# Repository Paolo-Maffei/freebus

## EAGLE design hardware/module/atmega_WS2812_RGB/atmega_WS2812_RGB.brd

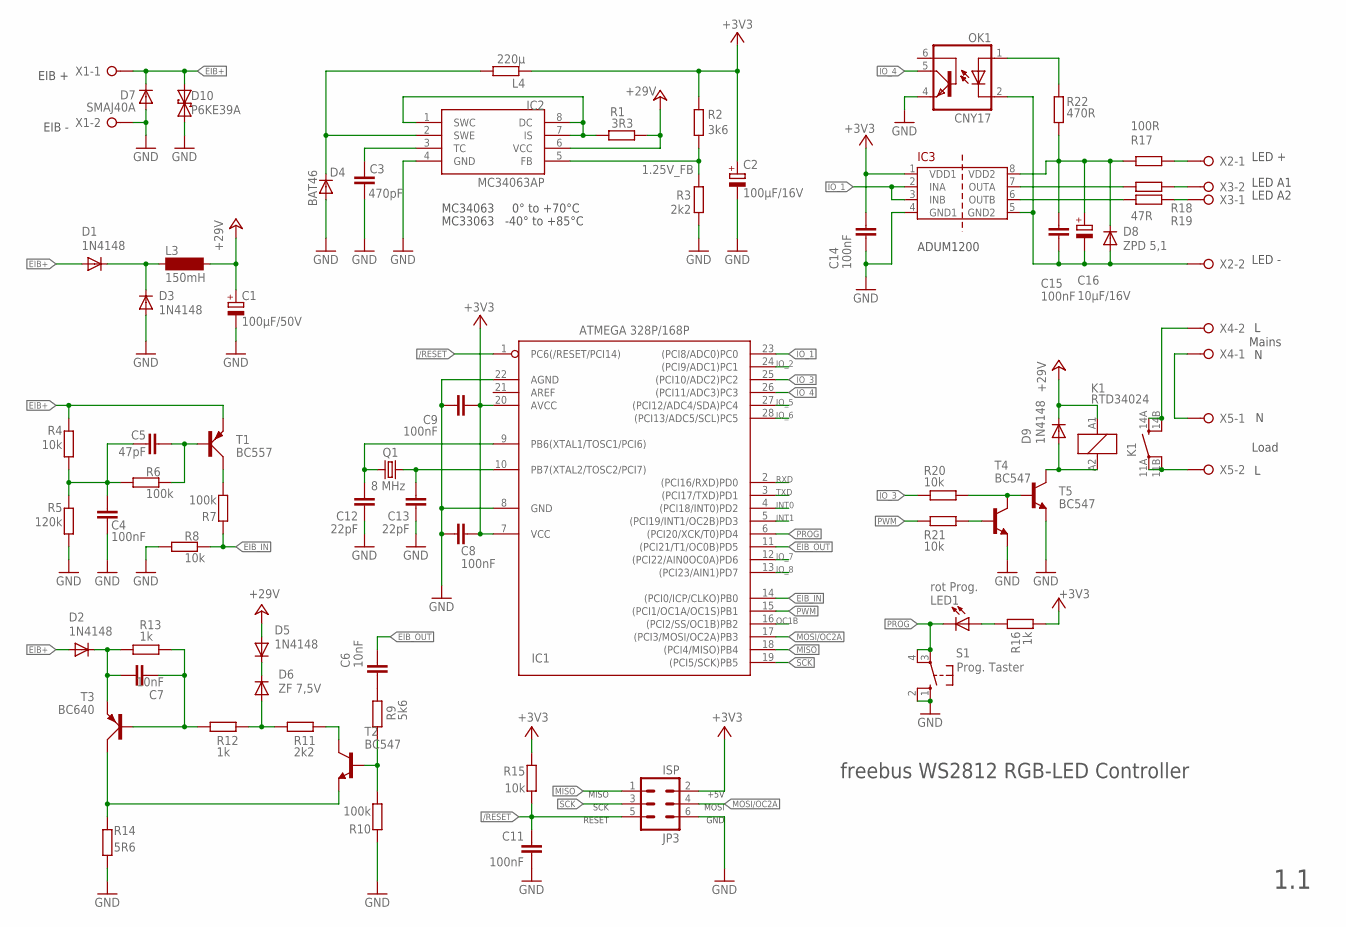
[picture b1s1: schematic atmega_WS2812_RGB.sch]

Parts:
C1: 100µF/50V; E3,5-8
C2: 100µF/16V; E3,5-8
C3: 470pF; C025-024X044
C4, C8, C9, C11, C14, C15: 100nF; C025-024X044
C5: 47pF; C025-024X044
C6, C7: 10nF; C025-024X044
C12, C13: 22pF; C025-024X044
C16: 10µF/16V; E2-5
D1, D2, D3, D5, D9: 1N4148; DO34-7R
D4: BAT46; DO34-7R
D6: ZF 7,5V; DO34-7R
D7: SMAJ40A; SMB
D8: ZPD 5,1; DO34-7R
D10: P6KE39A; DO41-7
IC1: ATMEGA 328P/168P; DIL28-3
IC2: MC34063AP; DIL08
IC3: ADUM1200; SO8
JP3: ISP; ML6
K1: RTD34024; RT-N/O16A5
L3: 150mH; BS11
L4: 220µ; 0309/12
LED1: rot Prog.; LED3MM
OK1: CNY17; DIL06
Q1: 8 MHz; HC49U-V
R1: 3R3; 0207/7
R2: 3k6; 0207/7
R3, R11: 2k2; 0207/7
R4, R8, R15, R20, R21: 10k; 0207/7
R5: 120k; 0207/7
R6, R7, R10: 100k; 0207/7
R9: 5k6; 0207/7
R12, R13, R16: 1k; 0207/7
R14: 5R6; 0207/7
R17: 100R; 0207/7
R18, R19: 47R; 0207/7
R22: 470R; 0207/7
S1: Prog. Taster; B3F-10XX
T1: BC557; SOT54A
T2, T4, T5: BC547; TO92
T3: BC640; SOT54D
X1, X2, X3, X4, X5: W237-02P; W237-132

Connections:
1.25V_FB: IC2.5 (FB), R2.2, R3.2
+3V3: C2.+, C8.1, C9.1, C14.2, IC1.7 (VCC), IC1.20 (AVCC), IC3.1 (VDD1), JP3.2, L4.1, R2.1, R15.2, R16.2
+24V: C1.+, D5.A, D9.C, IC2.6 (VCC), K1.A1 (1), L3.2, R1.1
/RESET: C11.2, IC1.1 (PC6(/RESET/PCI14)), JP3.5, R15.1
EIB+: D1.A, D2.A, D7.1 (C), D10.C (2), R4.2, T1.E, X1.1
EIB_IN: IC1.14 ((PCI0/ICP/CLKO)PB0), R7.2, R8.2
EIB_OUT: C6.2, IC1.11 ((PCI21/T1/OC0B)PD5)
GND: C1.-, C2.-, C3.1, C4.1, C8.2, C9.2, C11.1, C12.2, C13.2, C14.1, D3.A, D4.A, D7.2 (A), D10.A (1), IC1.8 (GND), IC1.22 (AGND), IC2.4 (GND), IC3.4 (GND1), JP3.6, OK1.4 (EMI), R3.1, R5.1, R8.1, R10.2, R14.1, S1.1 (S), S1.2 (S1), T4.1 (E), T5.1 (E), X1.2
INT0: IC1.4 ((PCI18/INT0)PD2)
INT1: IC1.5 ((PCI19/INT1/OC2B)PD3)
IO_1: IC1.23 ((PCI8/ADC0)PC0), IC3.2 (INA), IC3.3 (INB)
IO_2: IC1.24 ((PCI9/ADC1)PC1)
IO_3: IC1.25 ((PCI10/ADC2)PC2), R20.1
IO_4: IC1.26 ((PCI11/ADC3)PC3), OK1.5 (COL)
IO_5: IC1.27 ((PCI12/ADC4/SDA)PC4)
IO_6: IC1.28 ((PCI13/ADC5/SCL)PC5)
IO_7: IC1.12 ((PCI22/AIN0OC0A)PD6)
IO_8: IC1.13 ((PCI23/AIN1)PD7)
MISO: IC1.18 ((PCI4/MISO)PB4), JP3.1
MOSI/OC2A: IC1.17 ((PCI3/MOSI/OC2A)PB3), JP3.4
unnamed: R18.1, X3.2
unnamed: C15.2, C16.+, D8.C, IC3.8 (VDD2), R17.1, R22.1
unnamed: IC3.7 (OUTA), R18.2
unnamed: IC3.6 (OUTB), R19.2
unnamed: X4.1, X5.1
unnamed: R17.2, X2.1
unnamed: R21.2, T4.2 (B)
unnamed: R19.1, X3.1
unnamed: LED1.A, R16.1
unnamed: R20.2, T4.3 (C), T5.2 (B)
unnamed: K1.11A (PA), K1.11B (PB), X5.2
unnamed: C4.2, C5.1, R4.1, R5.2, R6.2
unnamed: R7.1, T1.C
unnamed: K1.14A (SA), K1.14B (SB), X4.2
unnamed: IC2.1 (SWC), IC2.7 (IS), IC2.8 (DC), R1.2
unnamed: D1.C, D3.C, L3.1
unnamed: C6.1, R9.1
unnamed: R9.2, R10.1, T2.2 (B)
unnamed: C7.2, R12.1, R13.1, T3.B
unnamed: OK1.1 (A), R22.2
unnamed: D5.C, D6.C
unnamed: D4.C, IC2.2 (SWE), L4.2
unnamed: C3.2, IC2.3 (TC)
unnamed: D6.A, R11.2, R12.2
unnamed: C5.2, R6.1, T1.B
unnamed: R11.1, T2.3 (C)
unnamed: R14.2, T2.1 (E), T3.C
unnamed: C7.1, D2.C, R13.2, T3.E
unnamed: C13.1, IC1.10 (PB7(XTAL2/TOSC2/PCI7)), Q1.2
unnamed: C12.1, IC1.9 (PB6(XTAL1/TOSC1/PCI6)), Q1.1
OC1B: IC1.16 ((PCI2/SS/OC1B)PB2)
PROG: IC1.6 ((PCI20/XCK/T0)PD4), LED1.K (C), S1.3, S1.4 (P1)
PWM: IC1.15 ((PCI1/OC1A/OC1S)PB1), R21.1
R4: D9.A, K1.A2 (2), T5.3 (C)
RXD: IC1.2 ((PCI16/RXD)PD0)
SCK: IC1.19 ((PCI5/SCK)PB5), JP3.3
TXD: IC1.3 ((PCI17/TXD)PD1)
WS2812_GND: C15.1, C16.-, D8.A, IC3.5 (GND2), OK1.2 (C), X2.2

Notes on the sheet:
MC34063 0° to +70°C
MC33063 -40° to +85°C
freebus WS2812 RGB-LED Controller
1.1
LED -
LED +
LED A1
LED A2
Mains
Load
ADUM1200
EIB +
EIB -

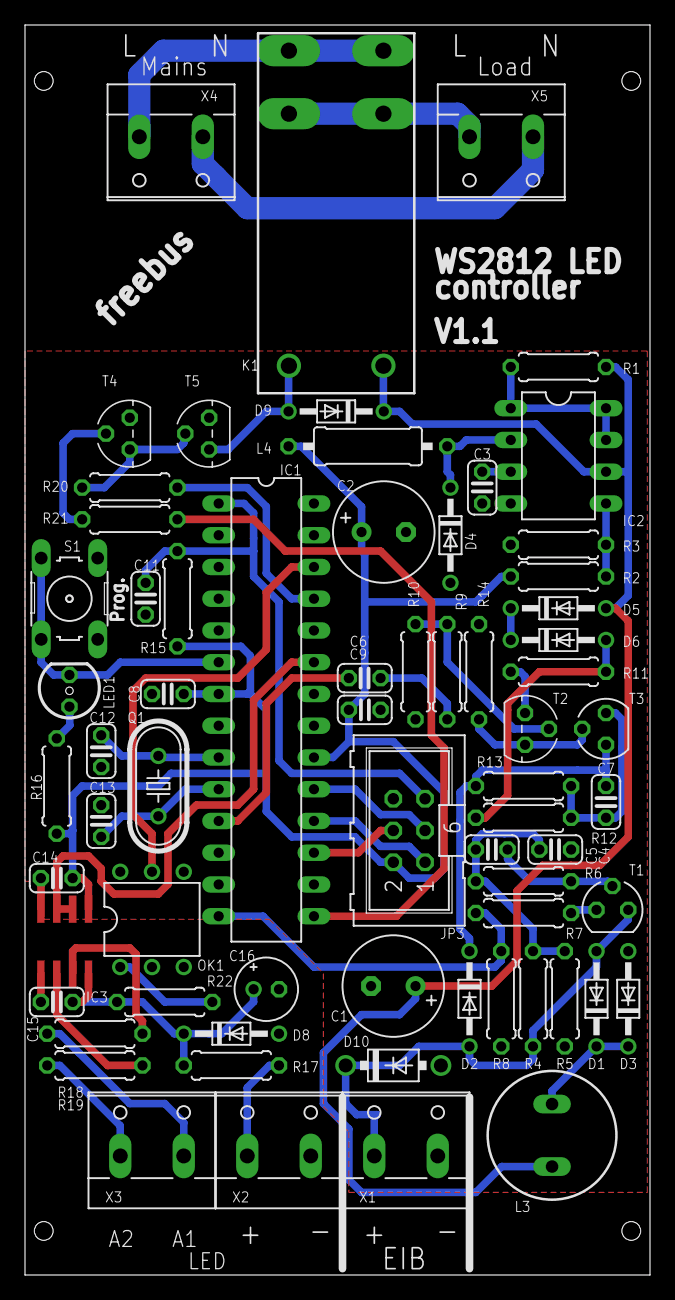
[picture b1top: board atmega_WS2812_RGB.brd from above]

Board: 2 copper layers, 50.0 x 100.0 mm, 68 parts (1 on the bottom side), 48 nets.

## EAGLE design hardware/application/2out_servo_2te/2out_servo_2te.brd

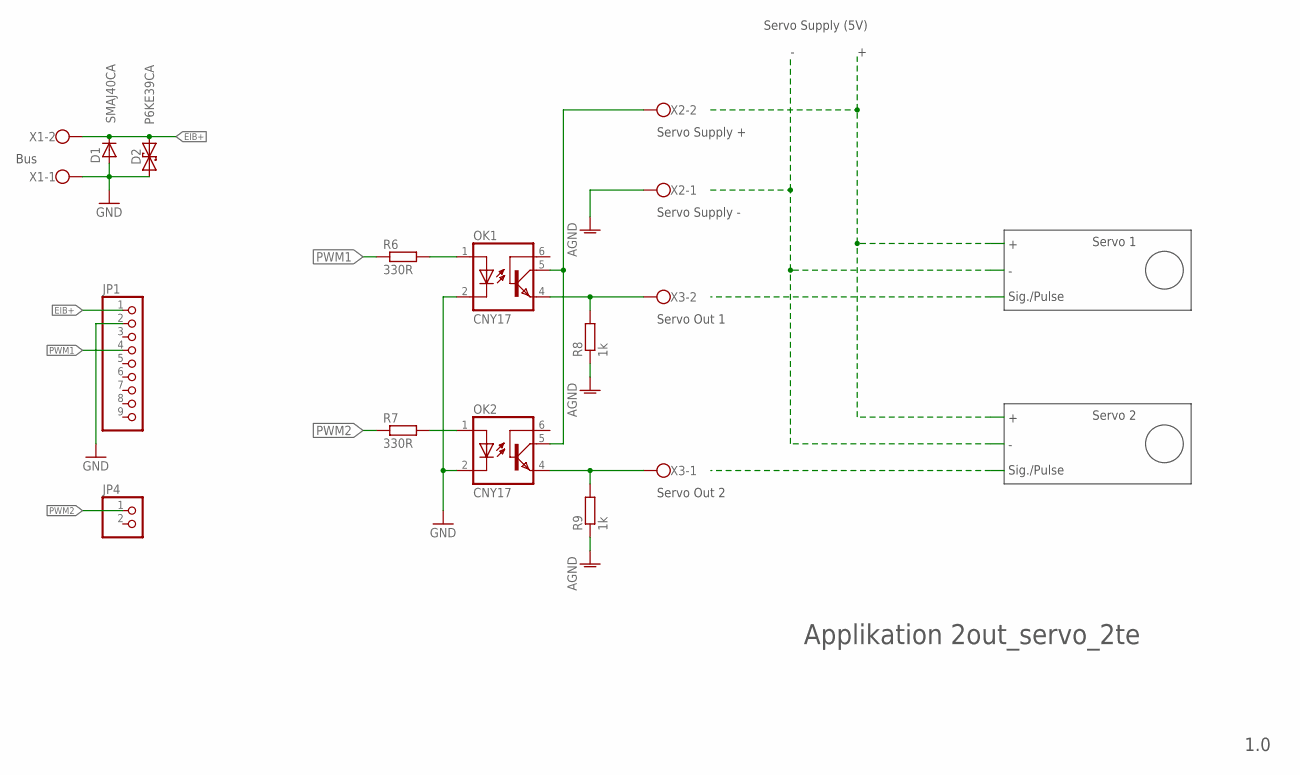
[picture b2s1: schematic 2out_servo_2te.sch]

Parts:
D1: SMAJ40CA; SOD87
D2: P6KE39CA; DO41-7
JP1: PINHD-1X9; 1X09
JP4: PINHD-1X2; 1X02
OK1, OK2: CNY17; DIL06
R6, R7: 330R; 0207/7
R8, R9: 1k; 0207/7
X1, X2, X3: W237-02P; W237-132

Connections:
AGND: R8.1, R9.1, X2.1
EIB+: D1.1 (C), D2.C (2), JP1.1, X1.2
GND: D1.2 (A), D2.A (1), JP1.2, OK1.2 (C), OK2.2 (C), X1.1
unnamed: OK2.1 (A), R7.2
unnamed: OK1.1 (A), R6.2
unnamed: OK1.4 (EMI), R8.2, X3.2
unnamed: OK2.4 (EMI), R9.2, X3.1
unnamed: OK1.5 (COL), OK2.5 (COL), X2.2
PWM1: JP1.4, R6.1
PWM2: JP4.1, R7.1

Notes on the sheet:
Bus
1.0
Applikation 2out_servo_2te
Servo 1
Sig./Pulse
Servo 2
Servo Supply +
Servo Supply -
Servo Out 1
Servo Out 2
Servo Supply (5V)

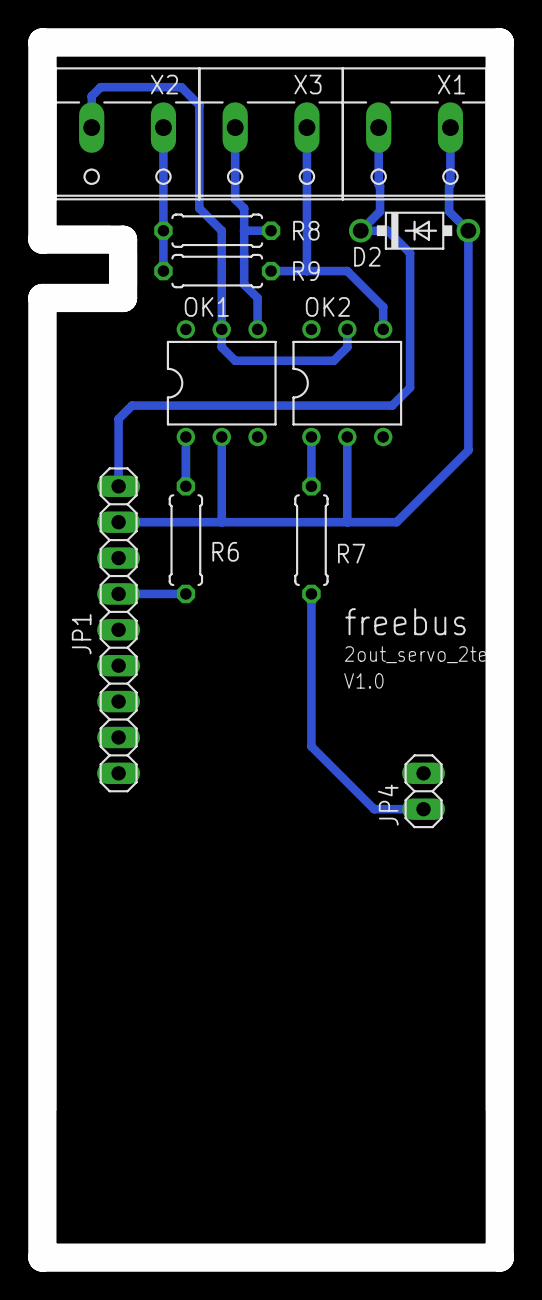
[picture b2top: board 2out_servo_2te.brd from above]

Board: 2 copper layers, 32.4 x 86.0 mm, 13 parts (1 on the bottom side), 10 nets.

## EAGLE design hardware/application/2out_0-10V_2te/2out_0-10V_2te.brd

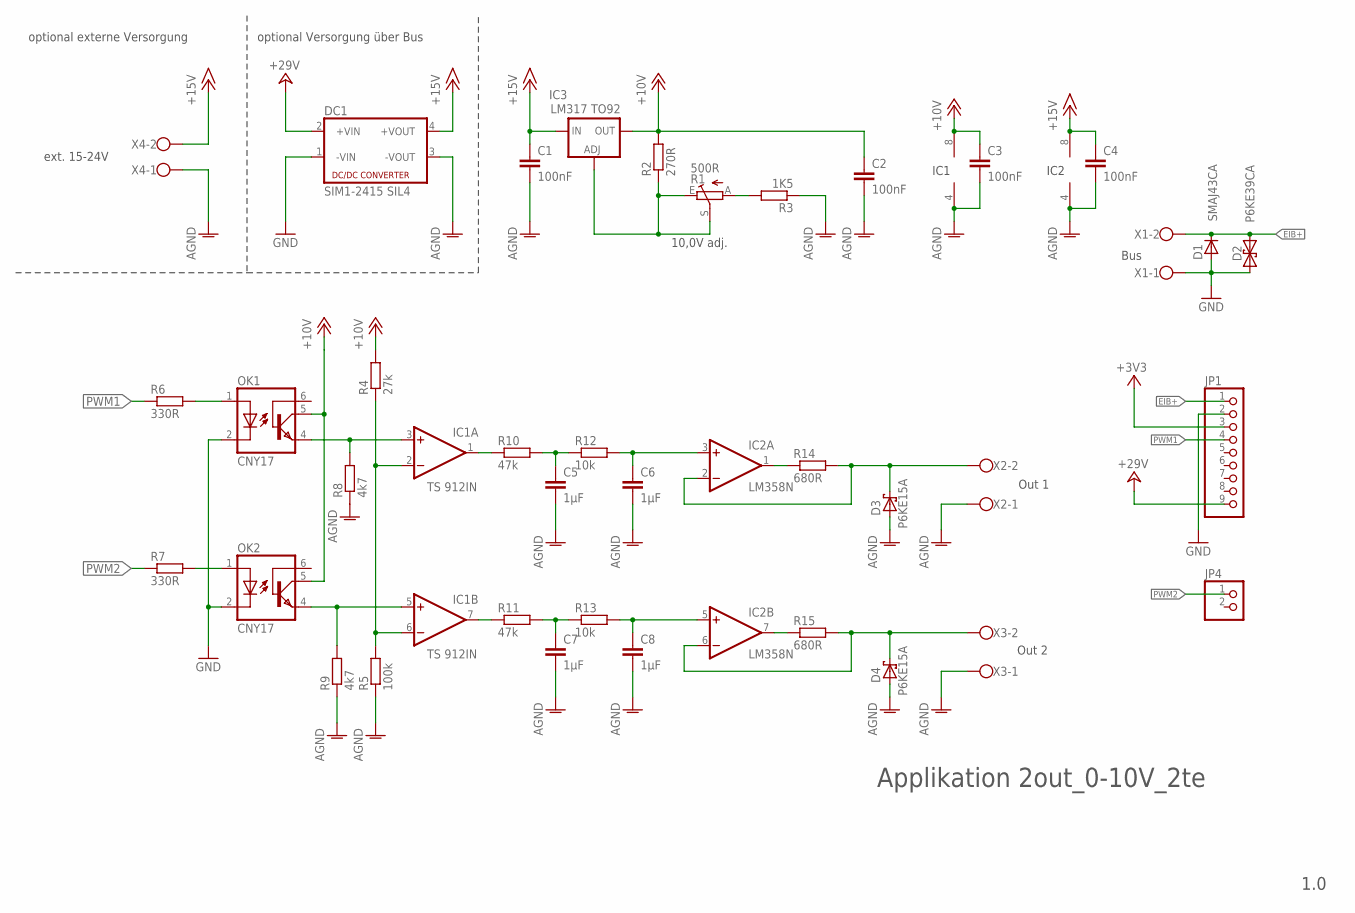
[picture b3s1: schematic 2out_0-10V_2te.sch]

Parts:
C1, C2, C3, C4: 100nF; C025-024X044
C5, C6, C7, C8: 1µF; C050-024X044
D1: SMAJ43CA; SOD87
D2: P6KE39CA; DO41-7
D3, D4: P6KE15A; DO41-7
DC1: SIM1-2415 SIL4; NME
IC1: TS 912IN; DIL08
IC2: LM358N; DIL08
IC3: LM317 TO92; 317L
JP1: PINHD-1X9; 1X09
JP4: PINHD-1X2; 1X02
OK1, OK2: CNY17; DIL06
R1: 500R; B64W
R2: 270R; 0207/7
R3: 1K5; 0207/7
R4: 27k; 0207/7
R5: 100k; 0207/7
R6, R7: 330R; 0207/7
R8, R9: 4k7; 0207/7
R10, R11: 47k; 0207/7
R12, R13: 10k; 0207/7
R14, R15: 680R; 0207/7
X1, X2, X3, X4: W237-02P; W237-132

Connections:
+3V3: JP1.3
+12V: C2.1, C3.1, IC1.8 (V+), IC3.2 (OUT), OK1.5 (COL), OK2.5 (COL), R2.2, R4.2
+15V: C1.1, C4.1, DC1.4 (+VOUT), IC2.8 (V+), IC3.3 (IN), X4.2
+29V: DC1.2 (+VIN), JP1.9
AGND: C1.2, C2.2, C3.2, C4.2, C5.2, C6.2, C7.2, C8.2, D3.A, D4.A, DC1.3 (-VOUT), IC1.4 (V-), IC2.4 (V-), R3.1, R5.1, R8.1, R9.1, X2.1, X3.1, X4.1
EIB+: D1.1 (C), D2.C (2), JP1.1, X1.2
GND: D1.2 (A), D2.A (1), DC1.1 (-VIN), JP1.2, OK1.2 (C), OK2.2 (C), X1.1
unnamed: IC1.7 (OUT), R11.1
unnamed: OK2.1 (A), R7.2
unnamed: OK1.1 (A), R6.2
unnamed: C7.1, R11.2, R13.1
unnamed: IC3.1 (ADJ), R1.E, R1.S, R2.1
unnamed: R1.A, R3.2
unnamed: IC1.3 (+IN), OK1.4 (EMI), R8.2
unnamed: IC1.2 (-IN), IC1.6 (-IN), R4.1, R5.2
unnamed: C8.1, IC2.5 (+IN), R13.2
unnamed: IC2.7 (OUT), R15.1
unnamed: IC1.5 (+IN), OK2.4 (EMI), R9.2
unnamed: IC1.1 (OUT), R10.1
unnamed: C5.1, R10.2, R12.1
unnamed: C6.1, IC2.3 (+IN), R12.2
unnamed: IC2.1 (OUT), R14.1
OUT_1: D3.C, IC2.2 (-IN), R14.2, X2.2
OUT_2: D4.C, IC2.6 (-IN), R15.2, X3.2
PWM1: JP1.4, R6.1
PWM2: JP4.1, R7.1

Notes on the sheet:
Bus
1.0
Applikation 2out_0-10V_2te
ext. 15-24V
Out 1
Out 2
optional externe Versorgung
optional Versorgung über Bus
10,0V adj.
IC1
IC2

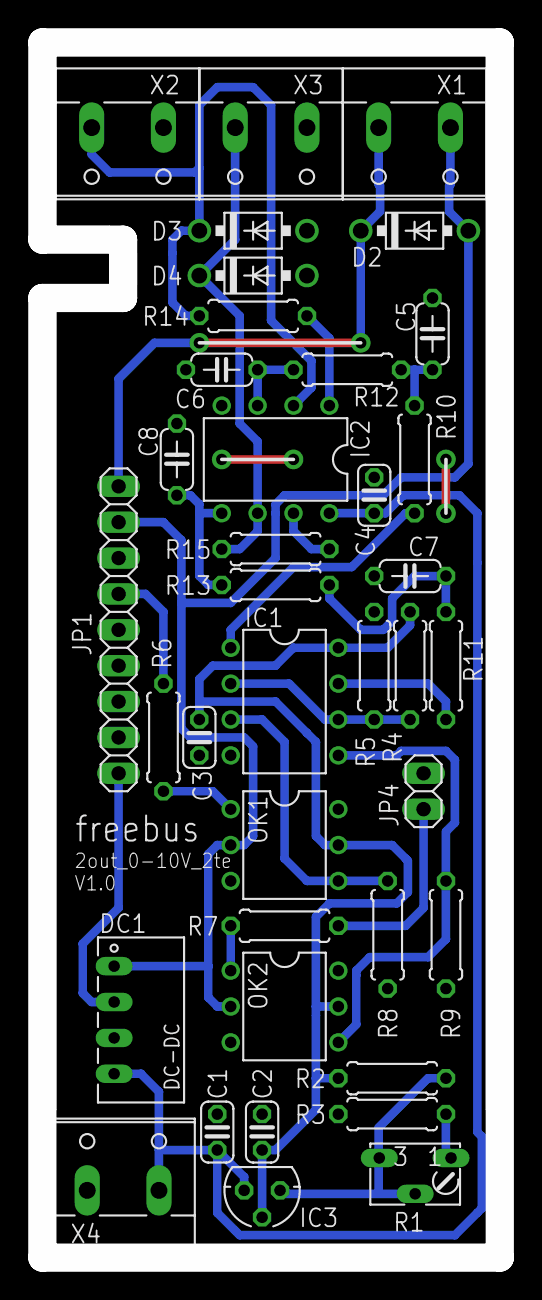
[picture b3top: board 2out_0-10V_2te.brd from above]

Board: 2 copper layers, 32.4 x 86.0 mm, 39 parts (1 on the bottom side), 25 nets.

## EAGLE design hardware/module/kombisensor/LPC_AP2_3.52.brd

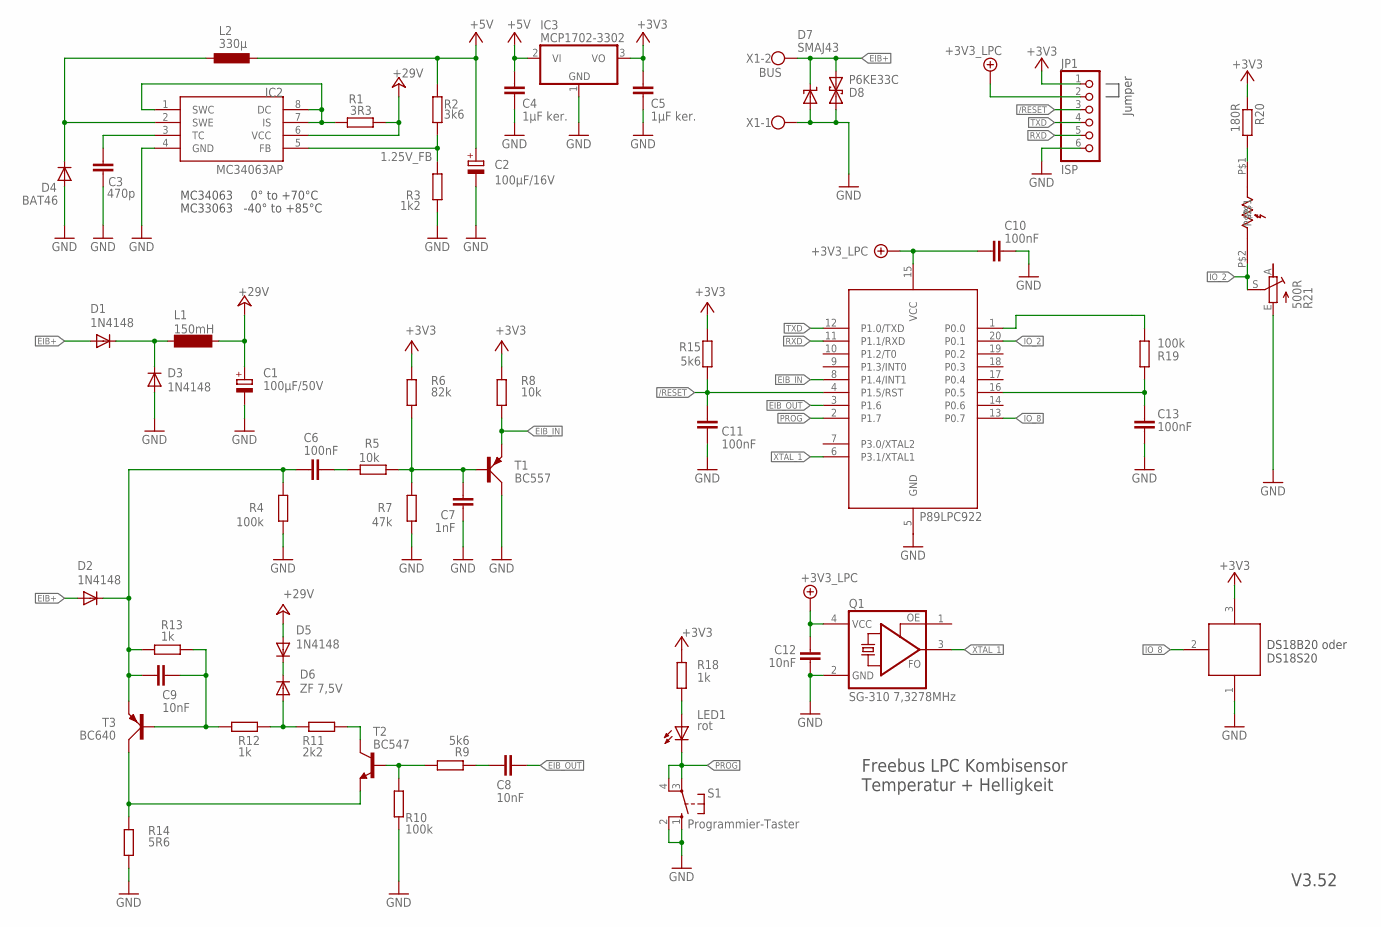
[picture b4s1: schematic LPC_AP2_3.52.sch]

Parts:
C1: 100µF/50V; E3,5-8
C2: 100µF/16V; E2-5
C3: 470p; C025-024X044
C4, C5: 1µF ker.; C050-024X044
C6, C11, C13: 100nF; C050-024X044
C7: 1nF; C050-024X044
C8, C9: 10nF; C050-024X044
C10: 100nF; C0805K
C12: 10nF; C0805K
D1, D3: 1N4148; D-2.5
D2: 1N4148; DO35-7
D4: BAT46; DO34-5R
D5: 1N4148; DO34-5R
D6: ZF 7,5V; DO34-5R
D7: SMAJ43; SMBJ
D8: P6KE33C; DO41-7
IC1: 89LPC922FN; DIL20
IC2: MC34063AP; DIL08
IC3: MCP1702-3302; TO92
IC4: DS18X20; DS18X
JP1: ISP; 1X06
L1: 150mH; SD12K100
L2: 330µ; 0207/7
LDR1: LDR07
LED1: rot; LED3MM
Q1: SG-310 7,3278MHz; ASF
R1: 3R3; 0207/2V
R2: 3k6; 0207/2V
R3: 1k2; 0207/2V
R4, R10: 100k; 0207/2V
R5, R8: 10k; 0207/2V
R6: 82k; 0207/2V
R7: 47k; 0207/2V
R9, R15: 5k6; 0207/2V
R11: 2k2; 0207/2V
R12: 1k; 0207/2V
R13, R18: 1k; 0207/7
R14: 5R6; 0207/2V
R19: 100k; 0207/7
R20: 180R; 0207/2V
R21: 500R; PT6L
S1: Programmier-Taster; B3F-10XX
T1: BC557; SOT54A
T2: BC547; TO92
T3: BC640; SOT54D
X1: BUS; W237-132

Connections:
1.25V_FB: IC2.5 (FB), R2.1, R3.2
+3V3: C5.1, IC3.3 (VO), IC4.3 (VDD), JP1.1, R6.2, R8.2, R15.2, R18.2, R20.1
+4.1V: C10.2, C12.1, IC1.15 (VCC), JP1.2, Q1.4 (VCC)
+5V: C2.+, C4.1, IC3.2 (VI), L2.1, R2.2
+24V: C1.+, D5.A, IC2.6 (VCC), L1.2, R1.1
/RESET: C11.2, IC1.4 (P1.5/RST), JP1.3, R15.1
EIB+: D1.A, D2.A, D7.C, D8.C (2), X1.2
EIB_IN: IC1.8 (P1.4/INT1), R8.1, T1.E
EIB_IN_OUT: C6.1, C9.1, D2.C, R4.2, R13.1, T3.E
EIB_OUT: C8.2, IC1.3 (P1.6)
GND: C1.-, C2.-, C3.1, C4.2, C5.2, C7.1, C10.1, C11.1, C12.2, C13.1, D3.A, D4.A, D7.A, D8.A (1), IC1.5 (GND), IC2.4 (GND), IC3.1 (GND), IC4.1 (GND), JP1.6, Q1.2 (GND), R3.1, R4.1, R7.2, R10.2, R14.1, R21.E, S1.1 (S), S1.2 (S1), T1.C, X1.1
IO_1: IC1.1 (P0.0), R19.1
IO_2: IC1.20 (P0.1), LDR1.P$2, R21.S
IO_6: C13.2, IC1.16 (P0.5), R19.2
IO_8: IC1.13 (P0.7), IC4.2 (IO)
unnamed: C8.1, R9.1
unnamed: C6.2, R5.2
unnamed: D6.A, R11.2, R12.2
unnamed: IC2.1 (SWC), IC2.7 (IS), IC2.8 (DC), R1.2
unnamed: R11.1, T2.3 (C)
unnamed: LDR1.P$1, R20.2
unnamed: R14.2, T2.1 (E), T3.C
unnamed: D1.C, D3.C, L1.1
unnamed: D5.C, D6.C
unnamed: D4.C, IC2.2 (SWE), L2.2
unnamed: R9.2, R10.1, T2.2 (B)
unnamed: C3.2, IC2.3 (TC)
unnamed: C7.2, R5.1, R6.1, R7.1, T1.B
unnamed: C9.2, R12.1, R13.2, T3.B
unnamed: LED1.A, R18.1
PROG: IC1.2 (P1.7), LED1.K (C), S1.3, S1.4 (P1)
RXD: IC1.11 (P1.1/RXD), JP1.5
TXD: IC1.12 (P1.0/TXD), JP1.4
XTAL_1: IC1.6 (P3.1/XTAL1), Q1.3 (FO)

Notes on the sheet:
Freebus LPC Kombisensor Temperatur + Helligkeit
P89LPC922
MC34063 0° to +70°C
MC33063 -40° to +85°C
Jumper
DS18B20 oder DS18S20
V3.52

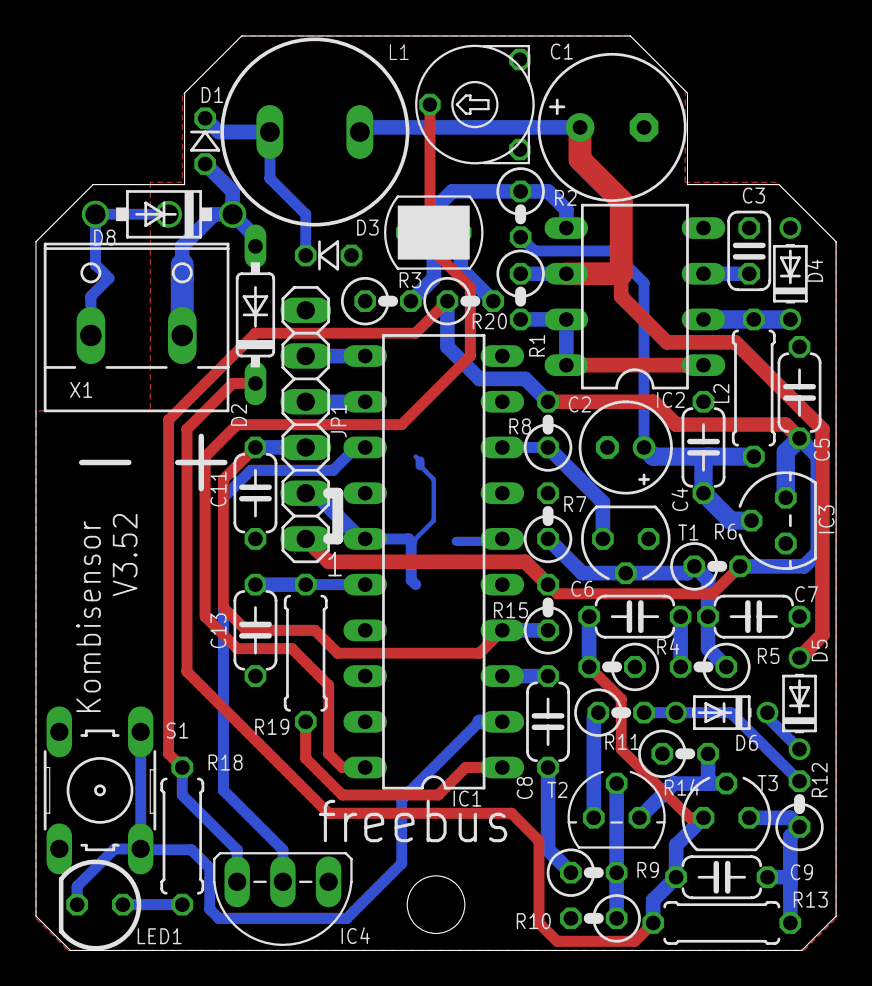
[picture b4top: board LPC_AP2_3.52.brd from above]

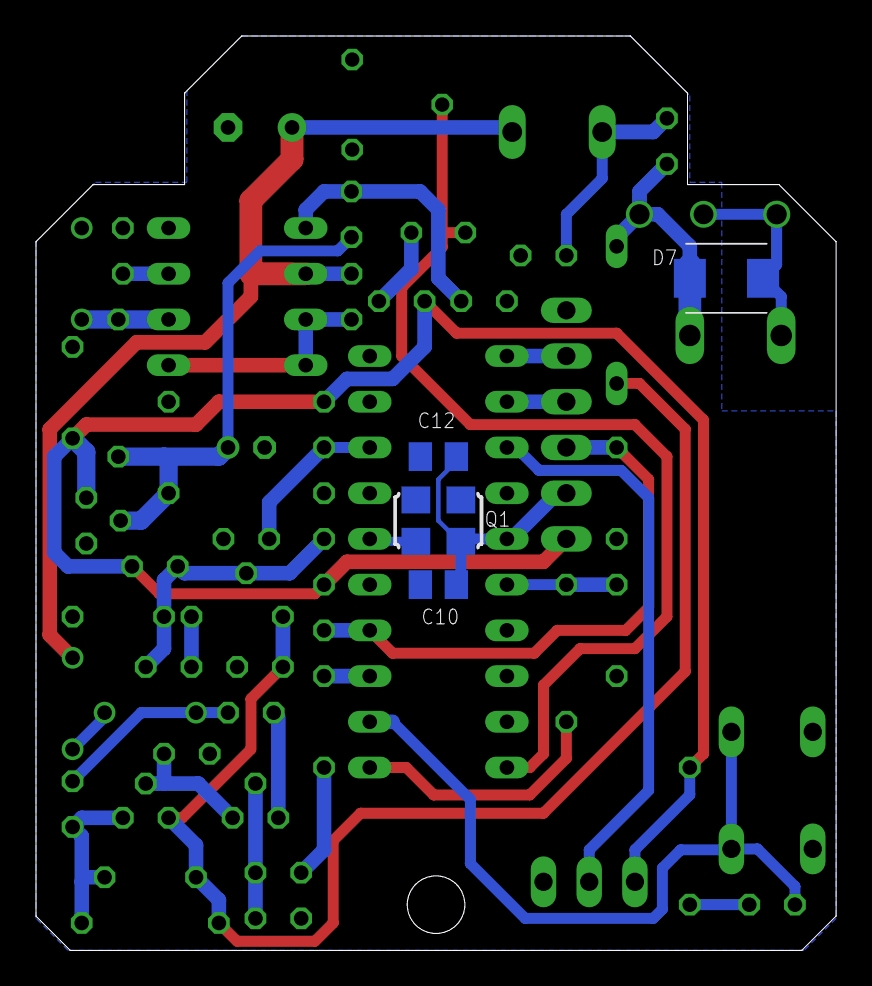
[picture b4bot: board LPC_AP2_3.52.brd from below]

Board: 2 copper layers, 44.5 x 50.8 mm, 55 parts (4 on the bottom side), 34 nets.

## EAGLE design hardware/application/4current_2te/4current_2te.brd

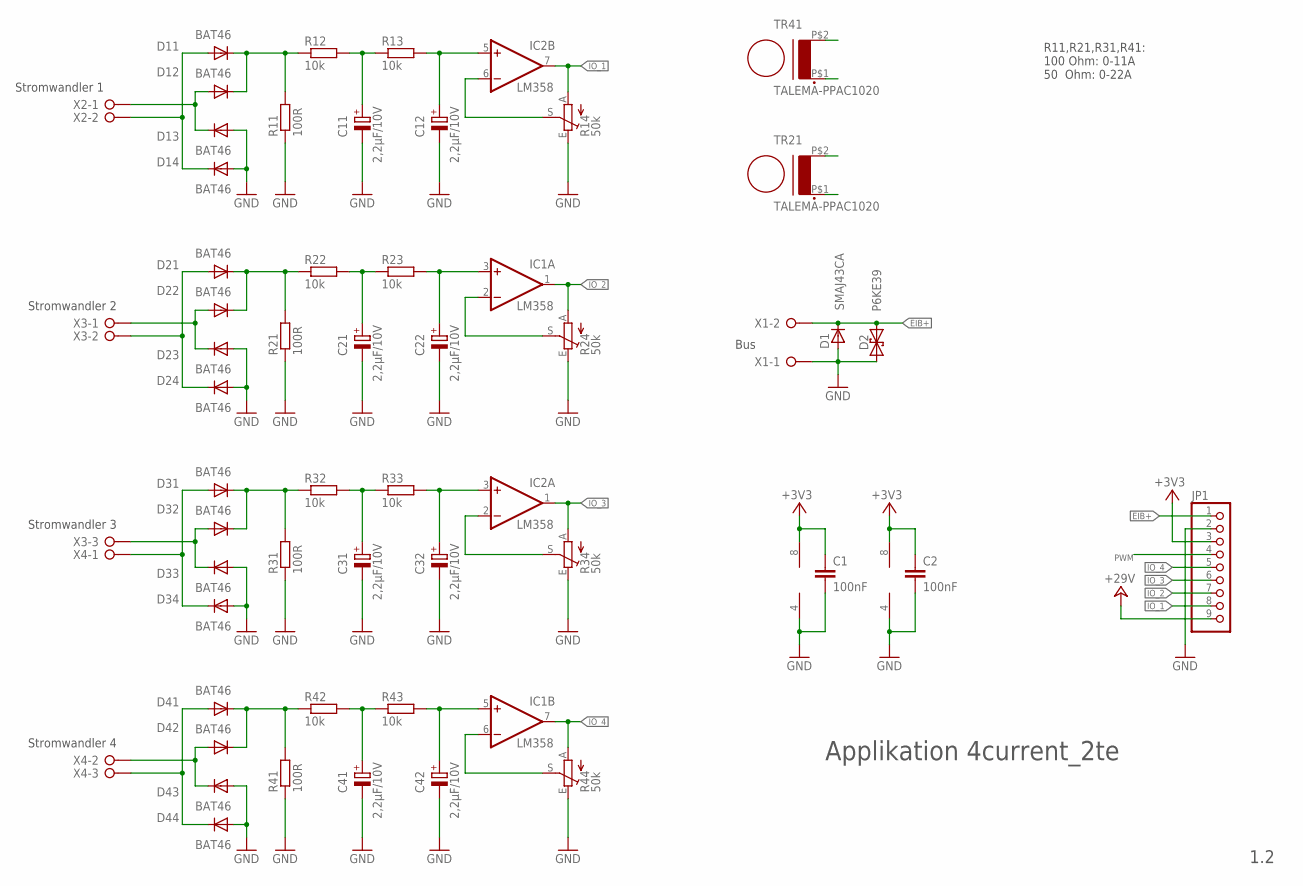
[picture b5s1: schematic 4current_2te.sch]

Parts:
C1, C2: 100nF; C025-024X044
C11, C12, C21, C22, C31, C32, C41, C42: 2,2µF/10V; E2-5
D1: SMAJ43CA; SOD87
D2: P6KE39; DO41-7
D11, D12, D13, D14, D21, D22, D23, D24, D31, D32, D33, D34, D41, D42, D43, D44: BAT46; DO35-7
IC1, IC2: LM358; DIL08
JP1: PINHD-1X9; 1X09
R11, R21, R31, R41: 100R; 0204/7
R12, R13, R22, R23, R32, R33, R42, R43: 10k; 0204/7
R14, R24, R34, R44: 50k; B64W
TR21, TR41: TALEMA-PPAC1020; TALEMA_AC
X1, X2: W237-02P; W237-132
X3, X4: W237-3E

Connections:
+3V3: C1.1, C2.1, IC1.8 (V+), IC2.8 (V+), JP1.3
+29V: JP1.9
EIB+: D1.1 (C), D2.C (2), JP1.1, X1.2
GND: C1.2, C2.2, C11.-, C12.-, C21.-, C22.-, C31.-, C32.-, C41.-, C42.-, D1.2 (A), D2.A (1), D13.A, D14.A, D23.A, D24.A, D33.A, D34.A, D43.A, D44.A, IC1.4 (V-), IC2.4 (V-), JP1.2, R11.1, R14.E, R21.1, R24.E, R31.1, R34.E, R41.1, R44.E, X1.1
IO_1: IC2.7 (OUT), JP1.8, R14.A
IO_2: IC1.1 (OUT), JP1.7, R24.A
IO_3: IC2.1 (OUT), JP1.6, R34.A
IO_4: IC1.7 (OUT), JP1.5, R44.A
unnamed: D21.C, D22.C, R21.2, R22.1
unnamed: C21.+, R22.2, R23.1
unnamed: C22.+, IC1.3 (+IN), R23.2
unnamed: IC1.2 (-IN), R24.S
unnamed: D31.C, D32.C, R31.2, R32.1
unnamed: C31.+, R32.2, R33.1
unnamed: C32.+, IC2.3 (+IN), R33.2
unnamed: D41.C, D42.C, R41.2, R42.1
unnamed: C41.+, R42.2, R43.1
unnamed: D11.C, D12.C, R11.2, R12.1
unnamed: C42.+, IC1.5 (+IN), R43.2
unnamed: IC1.6 (-IN), R44.S
unnamed: C11.+, R12.2, R13.1
unnamed: C12.+, IC2.5 (+IN), R13.2
unnamed: IC2.2 (-IN), R34.S
unnamed: IC2.6 (-IN), R14.S
PWM: JP1.4
SENSOR01: TR41.P$2 (S4)
SENSOR1_A: D12.A, D13.C, X2.1
SENSOR1_B: D11.A, D14.C, X2.2
SENSOR02: TR41.P$1 (S3)
SENSOR2_A: D22.A, D23.C, X3.1
SENSOR2_B: D21.A, D24.C, X3.2
SENSOR03: TR21.P$2 (S4)
SENSOR3_A: D32.A, D33.C, X3.3
SENSOR3_B: D31.A, D34.C, X4.1
SENSOR04: TR21.P$1 (S3)
SENSOR4_A: D42.A, D43.C, X4.2
SENSOR4_B: D41.A, D44.C, X4.3

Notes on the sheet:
Stromwandler 1
Stromwandler 2
Stromwandler 3
Stromwandler 4
R11,R21,R31,R41: 100 Ohm: 0-11A 50 Ohm: 0-22A
Bus
1.2
Applikation 4current_2te

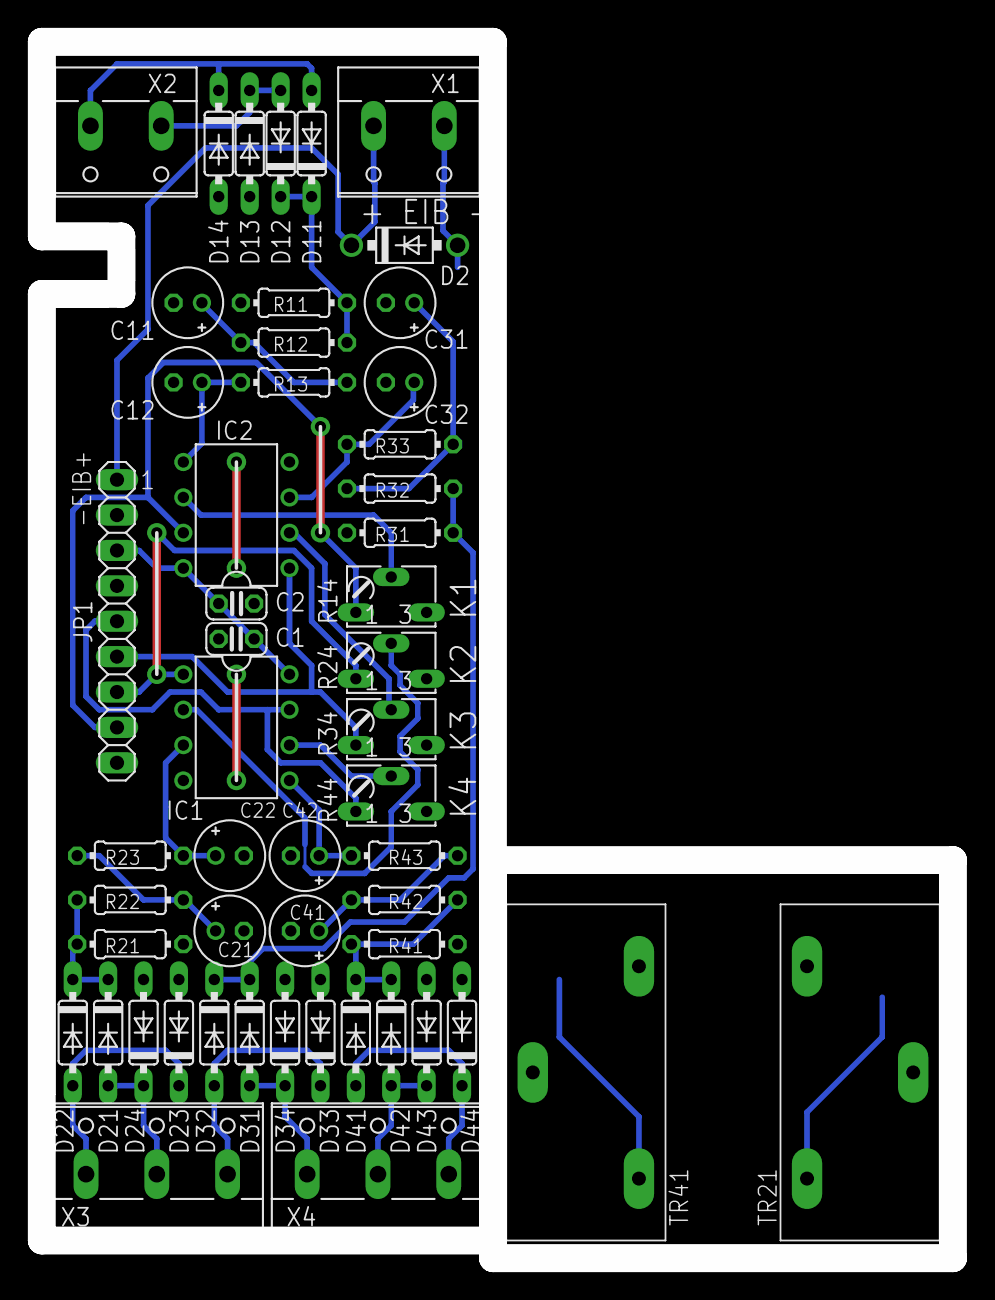
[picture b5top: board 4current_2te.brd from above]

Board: 2 copper layers, 65.4 x 87.3 mm, 53 parts (1 on the bottom side), 31 nets.

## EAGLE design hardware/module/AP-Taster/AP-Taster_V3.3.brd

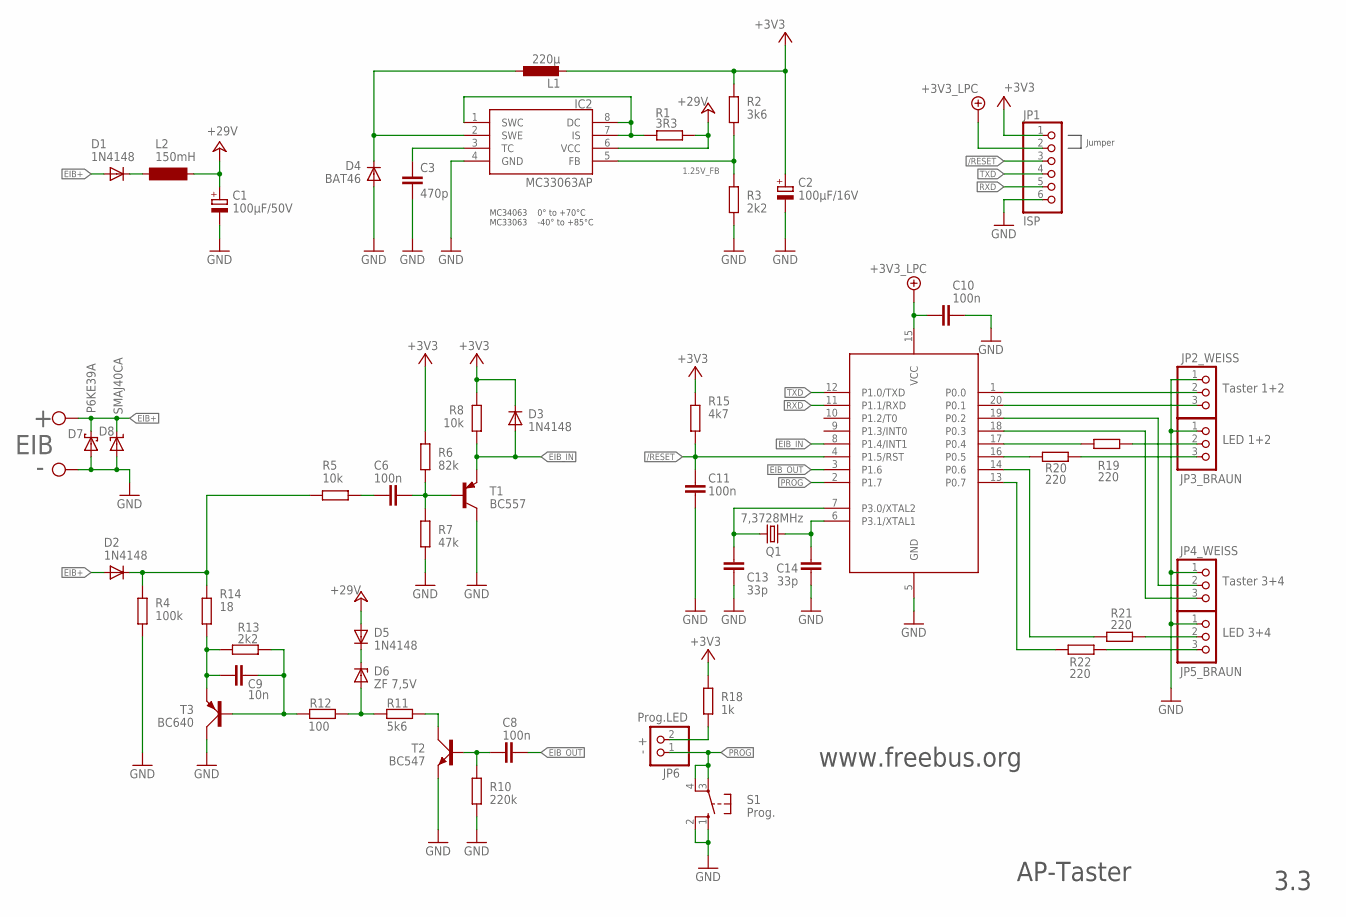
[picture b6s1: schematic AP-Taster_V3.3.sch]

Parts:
C1: 100µF/50V; E3,5-8
C2: 100µF/16V; E2-5
C3: 470p; C025-024X044
C6, C8: 100n; C050-024X044
C9: 10n; C025-024X044
C10, C11: 100n; C025-024X044
C13, C14: 33p; C025-024X044
D1, D2, D3, D5: 1N4148; DO34-7R
D4: BAT46; DO34-7R
D6: ZF 7,5V; DO34Z7R
D7: P6KE39A; DO35-7G
D8: SMAJ40CA; SMBJ
IC1: 89LPC922; DIL20
IC2: MC33063AP; DIL08
JP1: ISP; 1X06
JP2_WEISS: Taster 1+2; 1X03_CONNECTOR
JP3_BRAUN: LED 1+2; 1X03_CONNECTOR
JP4_WEISS: Taster 3+4; 1X03_CONNECTOR
JP5_BRAUN: LED 3+4; 1X03_CONNECTOR
JP6: Prog.LED; 1X02_CONNECTOR
L1: 220µ; 0207/10
L2: 150mH; BS11
Q1: 7,3728MHz; HC49/S
R1: 3R3; 0207/7
R2: 3k6; 0207/7
R3, R13: 2k2; 0207/7
R4: 100k; 0207/7
R5, R8: 10k; 0207/7
R6: 82k; 0207/7
R7: 47k; 0207/7
R10: 220k; 0207/7
R11: 5k6; 0207/7
R12: 100; 0207/7
R14: 18; 0207/7
R15: 4k7; 0207/7
R18: 1k; 0207/7
R19, R20, R21, R22: 220; 0207/7
S1: Prog.; B3F-10XX
T1: BC557; TO92
T2: BC547; SOT54A
T3: BC640; SOT54D
X1: EIB; W237-102

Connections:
1.25V_FB: IC2.5 (FB), R2.1, R3.2
+3V3: C2.+, D3.C, JP1.1, L1.2, R2.2, R6.1, R8.1, R15.1, R18.1
+3V3_LPC: C10.2, IC1.15 (VCC), JP1.2
+29V: C1.+, D5.A, IC2.6 (VCC), L2.2, R1.2
/RESET: C11.2, IC1.4 (P1.5/RST), JP1.3, R15.2
BASE1: C6.2, R6.2, R7.1, T1.2 (B)
EIB+: D1.A, D2.A, D7.C, D8.C, X1.2
EIB_IN: D3.A, IC1.8 (P1.4/INT1), R8.2, T1.1 (E)
EIB_OUT: C8.2, IC1.3 (P1.6)
FETGATE1: C8.1, R10.2, T2.B
GND: C1.-, C2.-, C3.2, C10.1, C11.1, C13.2, C14.2, D4.A, D7.A, D8.A, IC1.5 (GND), IC2.4 (GND), JP1.6, JP2_WEISS.1, JP3_BRAUN.1, JP4_WEISS.1, JP5_BRAUN.1, R3.1, R4.2, R7.2, R10.1, S1.1 (S), S1.2 (S1), T1.3 (C), T2.E, T3.C, X1.1
IO_1: IC1.1 (P0.0), JP2_WEISS.2
IO_2: IC1.20 (P0.1), JP2_WEISS.3
IO_3: IC1.19 (P0.2), JP4_WEISS.2
IO_4: IC1.18 (P0.3), JP4_WEISS.3
IO_5: IC1.17 (P0.4), R19.1
IO_6: IC1.16 (P0.5), R20.1
IO_7: IC1.14 (P0.6), R21.1
IO_8: IC1.13 (P0.7), R22.1
LED_1: JP3_BRAUN.2, R19.2
LED_2: JP3_BRAUN.3, R20.2
LED_3: JP5_BRAUN.2, R21.2
LED_4: JP5_BRAUN.3, R22.2
unnamed: D2.C, R4.1, R5.1, R14.1
unnamed: JP6.2, R18.2
unnamed: IC2.1 (SWC), IC2.7 (IS), IC2.8 (DC), R1.1
unnamed: D4.C, IC2.2 (SWE), L1.1
unnamed: C3.1, IC2.3 (TC)
unnamed: D1.C, L2.1
unnamed: D5.C, D6.C
unnamed: D6.A, R11.2, R12.2
unnamed: C9.1, R12.1, R13.1, T3.B
unnamed: C9.2, R13.2, R14.2, T3.E
unnamed: C6.1, R5.2
unnamed: R11.1, T2.C
PROG: IC1.2 (P1.7), JP6.1, S1.3, S1.4 (P1)
RXD: IC1.11 (P1.1/RXD), JP1.5
TXD: IC1.12 (P1.0/TXD), JP1.4
XTAL1: C14.1, IC1.6 (P3.1/XTAL1), Q1.1
XTAL2: C13.1, IC1.7 (P3.0/XTAL2), Q1.2

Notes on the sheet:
- +
3.3
www.freebus.org
AP-Taster
MC34063 0° to +70°C MC33063 -40° to +85°C
Jumper

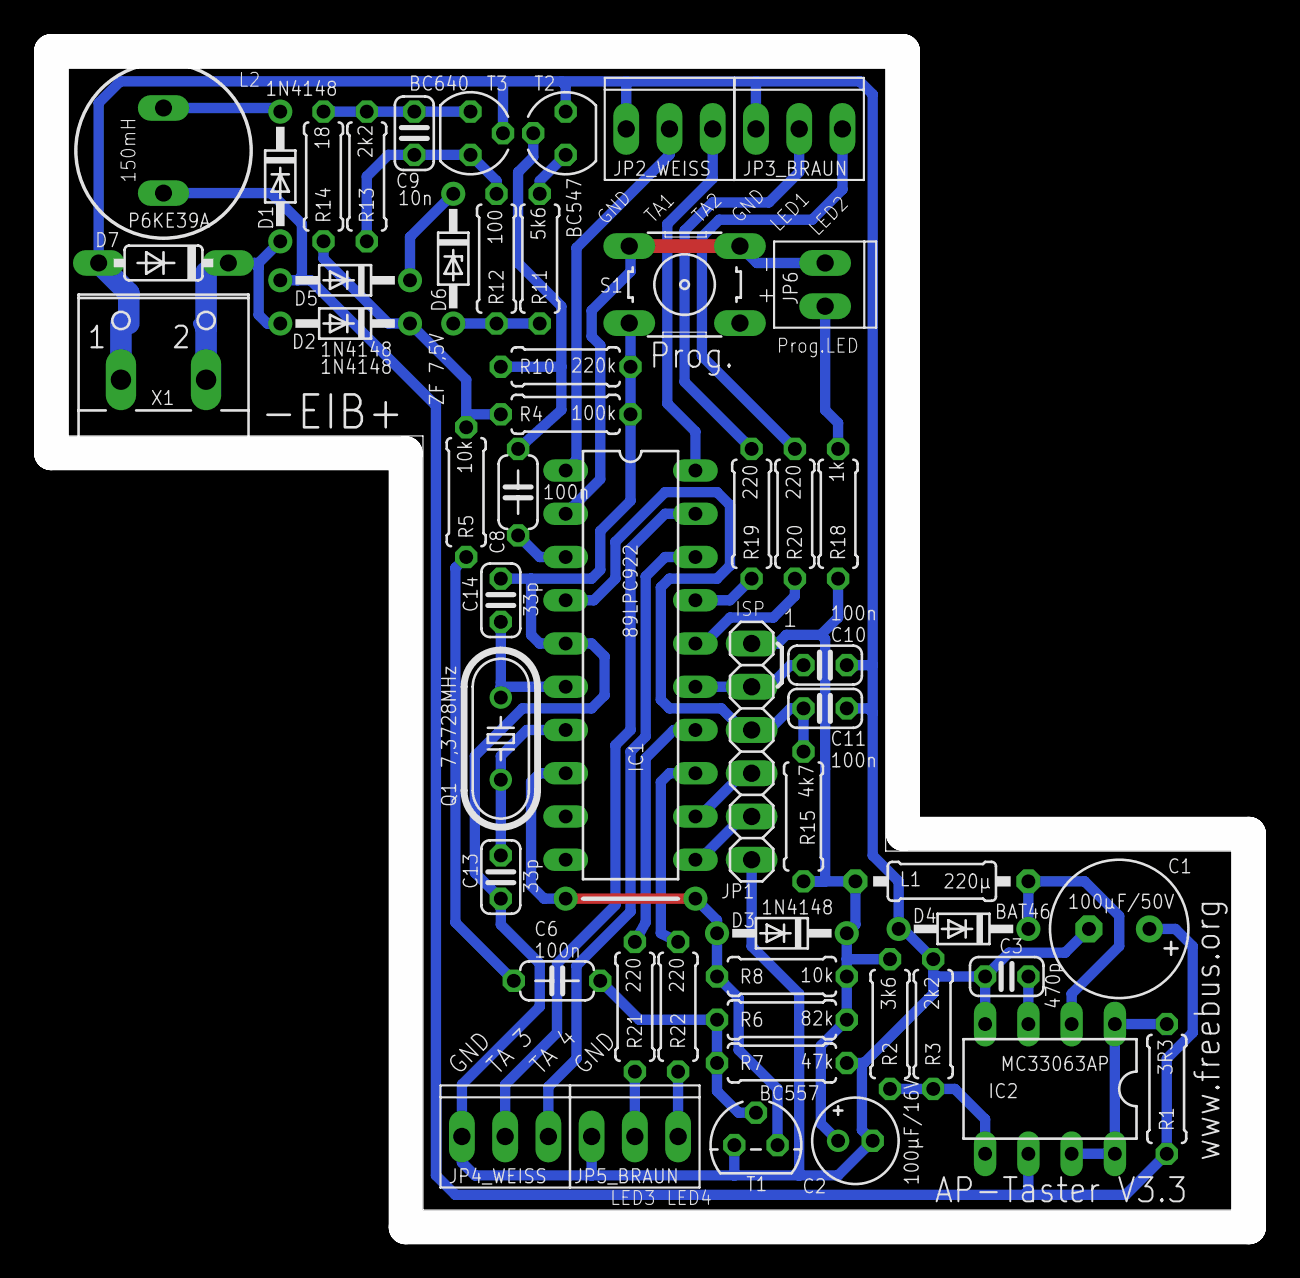
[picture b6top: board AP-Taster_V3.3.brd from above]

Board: 2 copper layers, 70.4 x 69.1 mm, 53 parts (1 on the bottom side), 40 nets.
